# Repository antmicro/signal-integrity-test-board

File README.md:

# Antmicro's Signal Integrity Test Board

Copyright (c) 2023 [Antmicro](https://www.antmicro.com)

## Overview

This project contains open hardware design files for a test board implementing various routing topologies.
The board can be used for calibrating and comparing measurements of signal propagation properties with Vector Network Analyzers (VNAs).
It can also be used for SI, EMI or EMC simulations with field solvers.
The board was designed in KiCad 6.x.

## Project structure

The main directory contains the KiCad design files, a LICENSE and a README.
The remaining files are stored in the following directories:

* ``img`` - contains graphics for this README
* ``doc`` - contains generated schematics and other documentation
* ``lib`` - contains KiCad component library
* ``assets`` - contains visual content used for showcasing the board on [Open Hardware Portal](https://openhardware.antmicro.com)

## Key features

* 4-layer PCB designed in defined impedance
* Includes SMA ports connected to copper primitives which implement the following features:

  * VNA calibration port terminated with 50Ohm
  * VNA calibration port open (i.e. not terminated)
  * VNA calibration port shorted (grounded) 
  * Single stripline
  * Differential pair stripline
  * Stripline with long stub
  * Stripline with short stub
  * Digital bandpass filter
  * Reference stripline layout with layer-change
  * Simple planar antenna
  * Not-terminated striplines with tight and loose meander of the same lengths

## License

This project is licensed under the [Apache-2.0](LICENSE) license.

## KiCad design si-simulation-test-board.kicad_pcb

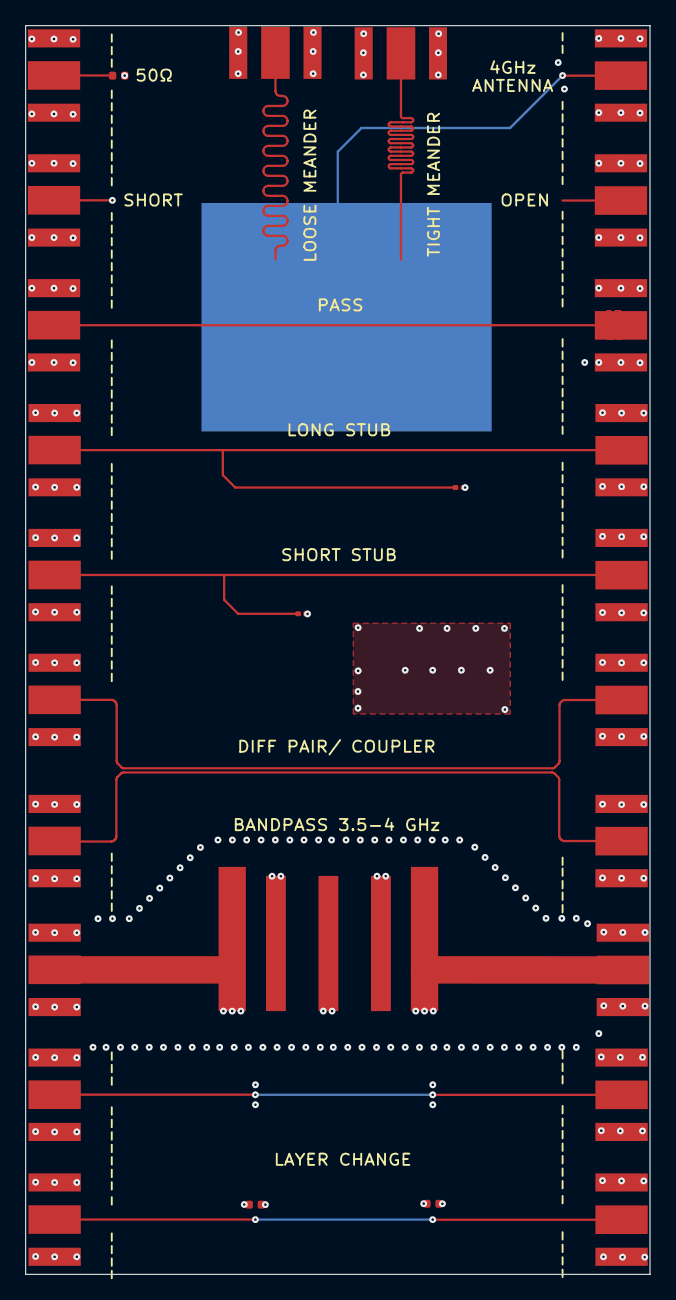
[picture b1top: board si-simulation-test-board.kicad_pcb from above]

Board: 4 copper layers, 50.0 x 100.0 mm, 27 parts (0 on the bottom side), 9 nets.

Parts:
C1, C2: C_100n_0402; C_0402_1005Metric
J1, J2, J3, J4, J5, J6, J7, J8, J9, J10, J11, J12, J13, J14, J15, J16, J17, J18, J19, J20, J21, J22: Conn_SMA_RF2-143-T-17-50-G; RF_SMA_BoardEdge_RF2-143-T-17-50-G
R2: R_50R_0402; R_0402_1005Metric
R3, R4: R_0R_0201; R_0201

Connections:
/DIFF_N: J12.1, J14.1
/DIFF_P: J11.1, J13.1
GND: C1.1, C1.2, C2.1, C2.2, J1.2, J2.2, J3.2, J4.1, J4.2, J5.2, J6.2, J7.2, J8.2, J9.2, J10.2, J11.2, J12.2, J13.2, J14.2, J15.2, J16.2, J17.2, J18.2, J19.1, J19.2, J20.1, J20.2, J21.2, J22.2, R2.2, R3.1, R4.1
unnamed: J1.1, J2.1
unnamed: J7.1, J8.1, R3.2
unnamed: J9.1, J10.1, R4.2
unnamed: J15.1, J17.1
unnamed: J16.1, J18.1
unnamed: J6.1, R2.1

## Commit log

2023-08-31 Add .gitignore
2023-08-31 Draft a schematic
2023-08-31 Route PCB WiP
2023-08-31 Finish PCB
2023-11-03 Correct silkscreen 'tight meander' text
2023-11-03 Improve schematic clarity
2023-11-03 Add gitignore
2023-11-03 Clean DRC, add missing cutouts for upper connectors, fix antenna feed point, standarize footprint, bump to 1.0.1
2023-11-03 Fix 3D model naming
2023-11-03 Make SCH A3 landscape
2023-11-03 Add local libraries
2023-11-03 Add LICENSE and basic README
2023-11-03 Add photo
2023-11-03 README: review
2023-11-07 Add OHP assets
2025-03-20 [#74509] Add SI assets
2025-03-21 [#74509] Update SI assets

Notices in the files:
parts and their libraries:
License: Apache-2.0
